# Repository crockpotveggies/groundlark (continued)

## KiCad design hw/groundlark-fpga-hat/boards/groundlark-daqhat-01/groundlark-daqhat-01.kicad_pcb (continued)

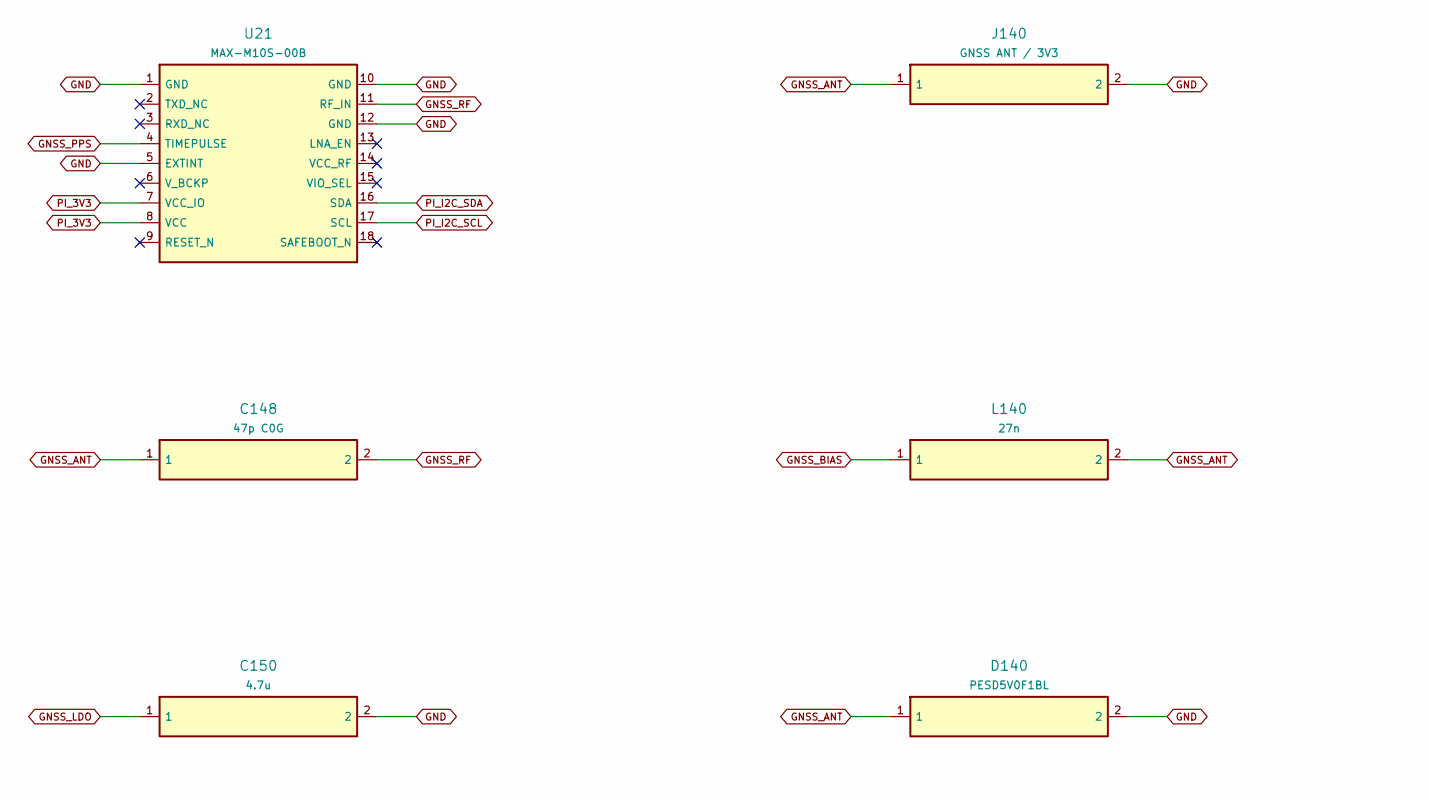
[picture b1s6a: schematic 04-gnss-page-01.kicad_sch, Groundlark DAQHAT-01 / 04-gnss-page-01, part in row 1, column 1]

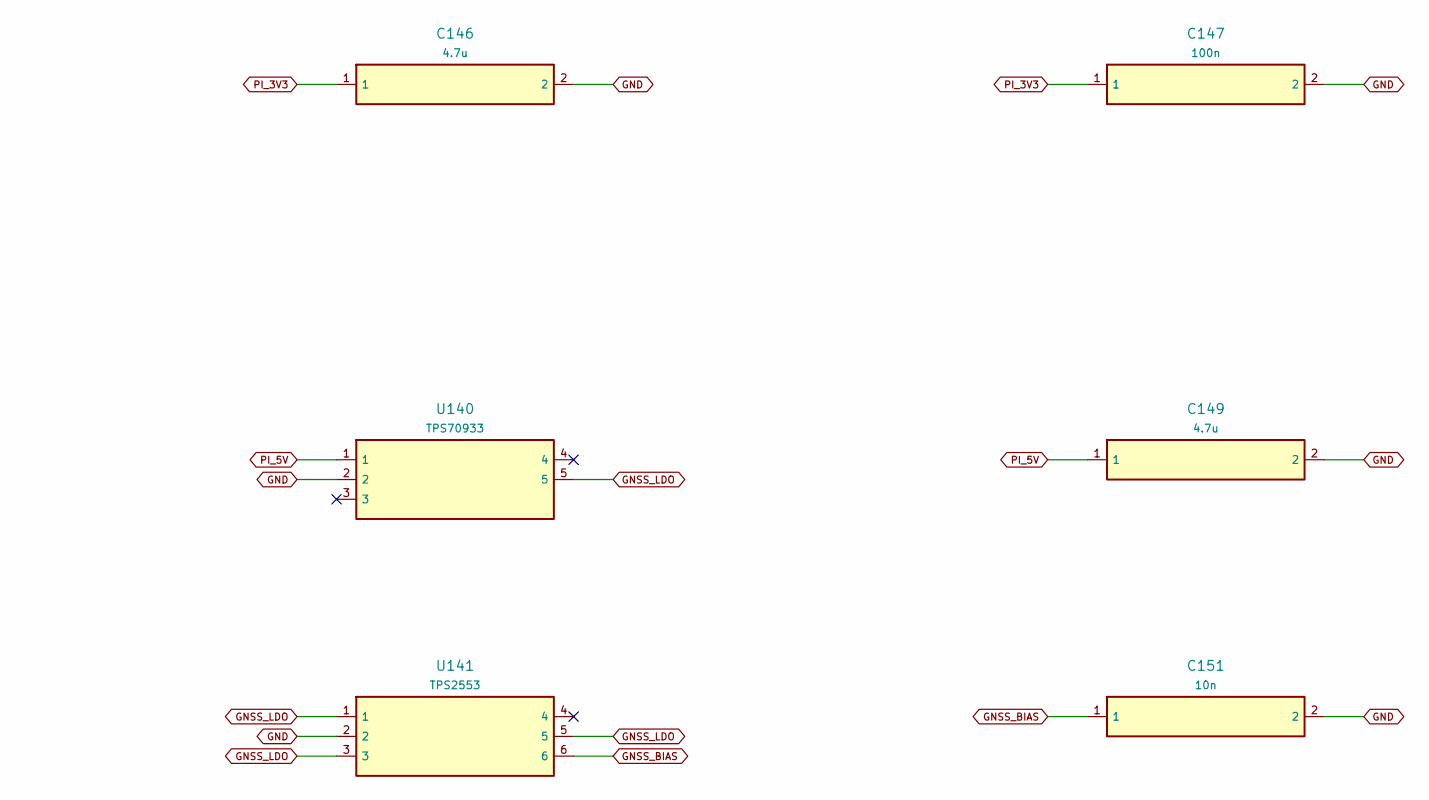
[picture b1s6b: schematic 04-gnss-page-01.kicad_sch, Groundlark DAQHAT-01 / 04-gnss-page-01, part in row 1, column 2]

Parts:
C146, C149, C150: 4.7u; Capacitor_SMD__C_0805_2012Metric; MPN GRM21BR71C475KA73L
C147: 100n; Capacitor_SMD__C_0603_1608Metric; MPN GRM188R71H104KA93D
C148: 47p C0G; GNSS_C0402; MPN GRM1555C1H470JA01D
C151: 10n; SUP_C_0603_1608Metric; MPN GRM188R71H103KA01D
D140: PESD5V0F1BL; GNSS_SOD882; MPN PESD5V0F1BL,315
J140: GNSS ANT / 3V3; GNSS_HL_SMA_KWE_02; MPN HL-SMA-KWE-02
L140: 27n; GNSS_L0402; MPN LQW15AN27NJ00D
U21: MAX-M10S-00B; RF_GPS__ublox_MAX; MPN MAX-M10S-00B
U140: TPS70933; SUP_SOT-23-5; MPN TPS70933DBVR
U141: TPS2553; GNSS_SOT23_6; MPN TPS2553DBVR

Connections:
GND: C146.2, C147.2, C149.2, C150.2, C151.2, D140.2, J140.2, U21.1 (GND), U21.5 (EXTINT), U21.10 (GND), U21.12 (GND), U140.2, U141.2; also elsewhere on the board
GNSS_ANT: C148.1, D140.1, J140.1, L140.2
GNSS_BIAS: C151.1, L140.1, U141.6
GNSS_FAULT_NC: U141.4
GNSS_LDO: C150.1, U140.5, U141.1, U141.3, U141.5; also elsewhere on the board
GNSS_PPS: U21.4 (TIMEPULSE); also elsewhere on the board
GNSS_RF: C148.2, U21.11 (RF_IN)
PI_3V3: C146.1, C147.1, U21.7 (VCC_IO), U21.8 (VCC); also elsewhere on the board
PI_5V: C149.1, U140.1; also elsewhere on the board
PI_I2C_SCL: U21.17 (SCL); also elsewhere on the board
PI_I2C_SDA: U21.16 (SDA); also elsewhere on the board
u21-2: U21.2 (TXD_NC)
u21-3: U21.3 (RXD_NC)
u21-6: U21.6 (V_BCKP)
u21-9: U21.9 (RESET_N)
u21-13: U21.13 (LNA_EN)
u21-14: U21.14 (VCC_RF)
u21-15: U21.15 (VIO_SEL)
u21-18: U21.18 (SAFEBOOT_N)
u140-3: U140.3
u140-4: U140.4

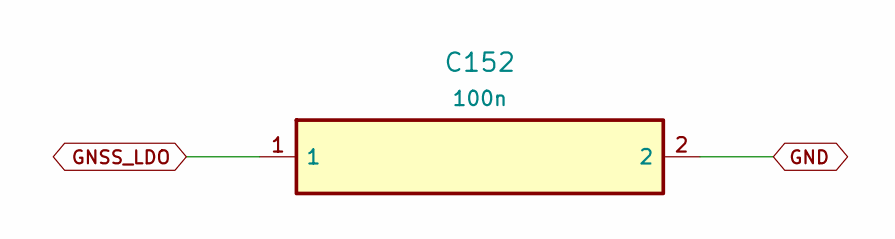
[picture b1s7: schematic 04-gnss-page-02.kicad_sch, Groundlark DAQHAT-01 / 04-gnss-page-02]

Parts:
C152: 100n; Capacitor_SMD__C_0603_1608Metric; MPN GRM188R71H104KA93D

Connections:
GND: C152.2; also elsewhere on the board
GNSS_LDO: C152.1; also elsewhere on the board

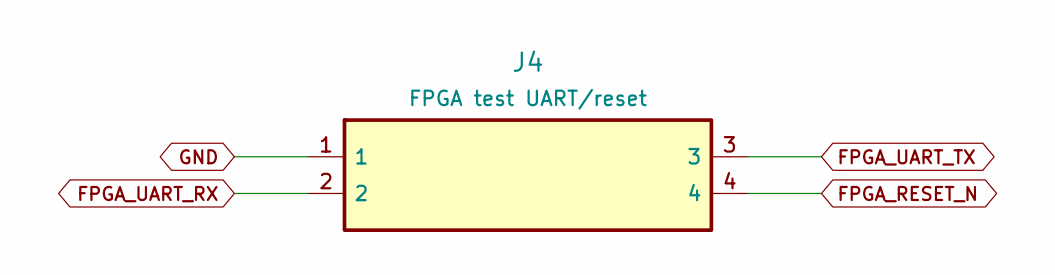
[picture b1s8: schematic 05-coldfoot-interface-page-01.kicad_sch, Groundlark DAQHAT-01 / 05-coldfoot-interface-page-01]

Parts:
J4: FPGA test UART/reset; Connector_PinHeader_2.54mm__PinHeader_1x04_P2.54mm_Vertical; MPN Coldfoot UART service ONLY

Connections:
FPGA_RESET_N: J4.4; also elsewhere on the board
FPGA_UART_RX: J4.2; also elsewhere on the board
FPGA_UART_TX: J4.3; also elsewhere on the board
GND: J4.1; also elsewhere on the board

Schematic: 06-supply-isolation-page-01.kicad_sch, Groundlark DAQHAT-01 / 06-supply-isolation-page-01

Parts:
C40: 10u; Capacitor_SMD__C_0805_2012Metric; MPN GRM21BR61A106KE19L
C41, C43, C44, C45, C46, C47: 100n; Capacitor_SMD__C_0603_1608Metric; MPN GRM188R71H104KA93D
C42: 22u; Capacitor_SMD__C_1206_3216Metric; MPN GRM31CR61A226KE19L
R50: 10k; Resistor_SMD__R_0603_1608Metric; MPN RC0603FR-0710KL
U40: TLV1117LV33DCYR; Package_TO_SOT_SMD__SOT-223-3_TabPin2; MPN TLV1117LV33DCYR
U41, U42: SN74LVC8T245PWR; Package_SO__TSSOP-24_4.4x7.8mm_P0.65mm; MPN SN74LVC8T245PWR

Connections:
GEO_DRDY_N: U42.16 (B6); also elsewhere on the board
GND: C40.2, C41.2, C42.2, C43.2, C44.2, C45.2, C46.2, C47.2, U40.1 (GND), U41.8 (A6), U41.9 (A7), U41.10 (A8), U41.11 (GND), U41.12 (GND), U41.13 (GND), U42.2 (DIR), U42.11 (GND), U42.12 (GND), U42.13 (GND), U42.14 (B8), U42.15 (B7), U42.17 (B5); also elsewhere on the board
IMU1_CS: U41.19 (B3); also elsewhere on the board
IMU1_INT: U42.20 (B2); also elsewhere on the board
IMU2_CS: U41.18 (B4); also elsewhere on the board
IMU2_INT: U42.19 (B3); also elsewhere on the board
IMU3_CS: U41.17 (B5); also elsewhere on the board
IMU3_INT: U42.18 (B4); also elsewhere on the board
PI_3V3: C44.1, C46.1, R50.2, U41.1 (VCCA), U41.2 (DIR), U42.1 (VCCA); also elsewhere on the board
PI_5V: C40.1, C41.1, U40.3 (IN); also elsewhere on the board
PI_GEO_DRDY_N: U42.8 (A6); also elsewhere on the board
PI_IMU1_CS: U41.5 (A3); also elsewhere on the board
PI_IMU1_INT: U42.4 (A2); also elsewhere on the board
PI_IMU2_CS: U41.6 (A4); also elsewhere on the board
PI_IMU2_INT: U42.5 (A3); also elsewhere on the board
PI_IMU3_CS: U41.7 (A5); also elsewhere on the board
PI_IMU3_INT: U42.6 (A4); also elsewhere on the board
PI_SPI_MISO: U42.3 (A1); also elsewhere on the board
PI_SPI_MOSI: U41.3 (A1); also elsewhere on the board
PI_SPI_SCLK: U41.4 (A2); also elsewhere on the board
SENSOR_OE_N: R50.1, U41.22 (OE_N), U42.22 (OE_N); also elsewhere on the board
SENS_3V3: C42.1, C43.1, C45.1, C47.1, U40.2 (OUT), U41.23 (VCCB), U41.24 (VCCB), U42.23 (VCCB), U42.24 (VCCB); also elsewhere on the board
SPI_MISO: U42.21 (B1); also elsewhere on the board
SPI_MOSI: U41.21 (B1); also elsewhere on the board
SPI_SCLK: U41.20 (B2); also elsewhere on the board
u41-14: U41.14 (B8)
u41-15: U41.15 (B7)
u41-16: U41.16 (B6)
u42-7: U42.7 (A5)
u42-9: U42.9 (A7)
u42-10: U42.10 (A8)

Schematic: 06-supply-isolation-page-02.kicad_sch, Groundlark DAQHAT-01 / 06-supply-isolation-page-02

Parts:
C48, C49: 100n; Capacitor_SMD__C_0603_1608Metric; MPN GRM188R71H104KA93D
R51: 100k; Resistor_SMD__R_0603_1608Metric; MPN RC0603FR-07100KL
R52, R53: 4.7k; Resistor_SMD__R_0603_1608Metric; MPN RC0603FR-074K7L
TP1: SENS_3V3; TestPoint__TestPoint_Pad_D1.5mm; MPN SENS_3V3
TP2: GND; TestPoint__TestPoint_Pad_D1.5mm; MPN GND
TP4: SENSOR_OE_N; TestPoint__TestPoint_Pad_D1.5mm; MPN SENSOR_OE_N
U43: ISO1640BDR; Package_SO__SOIC-8_3.9x4.9mm_P1.27mm; MPN ISO1640BDR

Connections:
GND: C48.2, C49.2, R51.2, TP2.1, U43.4 (GND1), U43.5 (GND2); also elsewhere on the board
I2C_SCL: R53.1, U43.3 (SCL1); also elsewhere on the board
I2C_SDA: R52.1, U43.2 (SDA1); also elsewhere on the board
PI_3V3: C49.1, U43.8 (VCC2); also elsewhere on the board
PI_I2C_SCL: U43.6 (SCL2); also elsewhere on the board
PI_I2C_SDA: U43.7 (SDA2); also elsewhere on the board
SENSOR_OE_N: TP4.1; also elsewhere on the board
SENS_3V3: C48.1, R52.2, R53.2, TP1.1, U43.1 (VCC1); also elsewhere on the board
SPI_MISO: R51.1; also elsewhere on the board

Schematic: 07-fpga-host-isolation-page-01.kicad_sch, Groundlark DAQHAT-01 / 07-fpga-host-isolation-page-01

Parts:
C75, C76, C77: 100n; Capacitor_SMD__C_0603_1608Metric; MPN GRM188R71H104KA93D
Q1: 2N7002; Package_TO_SOT_SMD__SOT-23; MPN 2N7002
R61: 47; Resistor_SMD__R_0603_1608Metric; MPN RC0603FR-0747RL
R62, R66: 100k; Resistor_SMD__R_0603_1608Metric; MPN RC0603FR-07100KL
R63, R64: 10k; Resistor_SMD__R_0603_1608Metric; MPN RC0603FR-0710KL
R65: 1k; Resistor_SMD__R_0603_1608Metric; MPN RC0603FR-071KL
U51: TXU0202DCUR; Package_SO__VSSOP-8_2.3x2mm_P0.5mm; MPN TXU0202DCUR
U52: TLV803EA30DBZR; Package_TO_SOT_SMD__SOT-23; MPN TLV803EA30DBZR

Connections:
FPGA_3V3: C76.1, C77.1, R63.2, R64.2, U51.7 (VCCB), U52.3 (VDD); also elsewhere on the board
FPGA_IO_ENABLE: R62.1, U51.6 (OE); also elsewhere on the board
FPGA_RESET_GATE: Q1.1 (G), R65.2, R66.1
FPGA_RESET_GPIO: R65.1; also elsewhere on the board
FPGA_RESET_N: Q1.3 (D), R64.1, U52.2 (RESET_N); also elsewhere on the board
FPGA_UART_DRIVE: R61.1, U51.8 (B1Y_OUT)
FPGA_UART_RX: R61.2, R63.1; also elsewhere on the board
FPGA_UART_TX: U51.1 (B2_IN); also elsewhere on the board
GND: C75.2, C76.2, C77.2, Q1.2 (S), R62.2, R66.2, U51.2 (GND), U52.1 (GND); also elsewhere on the board
PI_3V3: C75.1, U51.3 (VCCA); also elsewhere on the board
PI_UART_RX: U51.4 (A2Y_OUT); also elsewhere on the board
PI_UART_TX: U51.5 (A1_IN); also elsewhere on the board

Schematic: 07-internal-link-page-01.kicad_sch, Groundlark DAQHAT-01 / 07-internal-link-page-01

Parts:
C100, C101, C102, C103, C104, C105: 100n; Capacitor_SMD__C_0603_1608Metric; MPN GRM188R71H104KA93D
U100, U101: TMUX1574PWR; Package_SO__TSSOP-16_4.4x5mm_P0.65mm; MPN TMUX1574PWR
U102: TCA9534PWR; Package_SO__TSSOP-16_4.4x5mm_P0.65mm; MPN TCA9534PWR
U103: SN74LVC1G10DCKR; Package_TO_SOT_SMD__SOT-363_SC-70-6; MPN SN74LVC1G10DCKR
U104, U105: TLV809EA30DBZR; Package_TO_SOT_SMD__SOT-23; MPN TLV809EA30DBZR

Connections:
FPGA_3V3: C100.1, C101.1, C103.1, C105.1, U100.16 (VDD), U101.16 (VDD), U103.5 (VCC), U105.3 (VDD); also elsewhere on the board
FPGA_LINK_CS_N: U101.2 (S1A); also elsewhere on the board
FPGA_LINK_DQ0: U100.5 (S2A); also elsewhere on the board
FPGA_LINK_DQ1: U100.11 (S3A); also elsewhere on the board
FPGA_LINK_DQ2: U100.14 (S4A); also elsewhere on the board
FPGA_LINK_DQ3: U101.5 (S2A); also elsewhere on the board
FPGA_LINK_SCLK: U100.2 (S1A); also elsewhere on the board
GND: C100.2, C101.2, C102.2, C103.2, C104.2, C105.2, U100.8 (GND), U101.8 (GND), U101.9 (D3), U101.10 (S3B), U101.11 (S3A), U101.12 (D4), U101.13 (S4B), U101.14 (S4A), U102.1 (A0), U102.2 (A1), U102.3 (A2), U102.6 (P2), U102.7 (P3), U102.8 (GND), U102.9 (P4), U102.10 (P5), U102.11 (P6), U102.12 (P7), U103.2 (GND), U104.1 (GND), U105.1 (GND); also elsewhere on the board
JTAG_TCK: U100.3 (S1B); also elsewhere on the board
JTAG_TDI: U100.6 (S2B); also elsewhere on the board
JTAG_TDO: U100.10 (S3B); also elsewhere on the board
JTAG_TMS: U100.13 (S4B); also elsewhere on the board
LINK_ARMED_REQUEST: U103.1 (A); also elsewhere on the board
LINK_CS_N: U101.4 (D1); also elsewhere on the board
LINK_DQ0: U100.7 (D2); also elsewhere on the board
LINK_DQ1: U100.9 (D3); also elsewhere on the board
LINK_DQ2: U100.12 (D4); also elsewhere on the board
LINK_DQ3: U101.7 (D2); also elsewhere on the board
LINK_FPGA_GOOD: U103.6 (C), U105.2 (RESET_N); also elsewhere on the board
LINK_JTAG_SEL: U100.1 (SEL), U101.1 (SEL), U102.4 (P0_MODE); also elsewhere on the board
LINK_OE_N: U100.15 (EN_N), U101.15 (EN_N), U103.4 (Y); also elsewhere on the board
LINK_PI_GOOD: U103.3 (B), U104.2 (RESET_N); also elsewhere on the board
LINK_REQUEST: U102.5 (P1_ENABLE); also elsewhere on the board
LINK_SCLK: U100.4 (D1); also elsewhere on the board
PI_3V3: C102.1, C104.1, U102.16 (VCC), U104.3 (VDD); also elsewhere on the board
PI_I2C_SCL: U102.14 (SCL); also elsewhere on the board
PI_I2C_SDA: U102.15 (SDA); also elsewhere on the board
u101-3: U101.3 (S1B)
u101-6: U101.6 (S2B)
u102-13: U102.13 (INT_N)

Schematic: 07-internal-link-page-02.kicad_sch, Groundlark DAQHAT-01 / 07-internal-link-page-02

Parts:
R100, R101, R102, R103, R104, R105: 22; Resistor_SMD__R_0603_1608Metric; MPN RC0603FR-0722RL
R106, R107, R108, R109, R110, R111: 10k; Resistor_SMD__R_0603_1608Metric; MPN RC0603FR-0710KL

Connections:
FPGA_3V3: R108.2, R111.2; also elsewhere on the board
FPGA_LINK_CS_N: R111.1; also elsewhere on the board
GND: R106.2, R107.2, R109.2, R110.2; also elsewhere on the board
LINK_CS_N: R104.2; also elsewhere on the board
LINK_DQ0: R101.2; also elsewhere on the board
LINK_DQ1: R102.2; also elsewhere on the board
LINK_DQ2: R103.2; also elsewhere on the board
LINK_DQ3: R105.2; also elsewhere on the board
LINK_FPGA_GOOD: R110.1; also elsewhere on the board
LINK_JTAG_SEL: R106.1; also elsewhere on the board
LINK_OE_N: R108.1; also elsewhere on the board
LINK_PI_GOOD: R109.1; also elsewhere on the board
LINK_REQUEST: R107.1; also elsewhere on the board
LINK_SCLK: R100.2; also elsewhere on the board
PI_LINK_CS_N: R104.1; also elsewhere on the board
PI_LINK_DQ0: R101.1; also elsewhere on the board
PI_LINK_DQ1: R102.1; also elsewhere on the board
PI_LINK_DQ2: R103.1; also elsewhere on the board
PI_LINK_DQ3: R105.1; also elsewhere on the board
PI_LINK_SCLK: R100.1; also elsewhere on the board

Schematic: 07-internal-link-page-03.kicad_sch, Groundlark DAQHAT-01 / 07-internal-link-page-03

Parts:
C106: 100n; Capacitor_SMD__C_0603_1608Metric; MPN GRM188R71H104KA93D
R112, R114, R116, R117: 100k; Resistor_SMD__R_0603_1608Metric; MPN RC0603FR-07100KL
R113, R115: 10k; Resistor_SMD__R_0603_1608Metric; MPN RC0603FR-0710KL
U106: SN74LVC1G08DCKR; Package_TO_SOT_SMD__SOT-353_SC-70-5; MPN SN74LVC1G08DCKR

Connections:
FPGA_3V3: C106.1, R113.2, R115.2, U106.5 (VCC); also elsewhere on the board
FPGA_IO_ENABLE: U106.2 (B); also elsewhere on the board
FPGA_LINK_DQ2: R116.1; also elsewhere on the board
FPGA_LINK_DQ3: R117.1; also elsewhere on the board
FPGA_LINK_SCLK: R112.1; also elsewhere on the board
GND: C106.2, R112.2, R114.2, R116.2, R117.2, U106.3 (GND); also elsewhere on the board
JTAG_TCK: R114.1; also elsewhere on the board
JTAG_TDI: R115.1; also elsewhere on the board
JTAG_TMS: R113.1; also elsewhere on the board
LINK_ARMED_REQUEST: U106.4 (Y); also elsewhere on the board
LINK_REQUEST: U106.1 (A); also elsewhere on the board

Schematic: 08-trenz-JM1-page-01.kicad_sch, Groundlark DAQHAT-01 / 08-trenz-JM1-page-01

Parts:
J80: LSHM-150-04.0-L-DV-A-S-K-TR; TZ_TZ100; MPN LSHM-150-04.0-L-DV-A-S-K-TR

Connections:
3: J80.3
5: J80.5
9: J80.9
11: J80.11
15: J80.15
17: J80.17
18: J80.18
20: J80.20
21: J80.21
22: J80.22
23: J80.23
24: J80.24
26: J80.26
28: J80.28
32: J80.32
34: J80.34
35: J80.35
36: J80.36
37: J80.37
38: J80.38
39: J80.39
40: J80.40
41: J80.41
42: J80.42
44: J80.44
45: J80.45
46: J80.46
47: J80.47
48: J80.48
49: J80.49
50: J80.50
51: J80.51
52: J80.52
55: J80.55
56: J80.56
57: J80.57
58: J80.58
59: J80.59
60: J80.60
61: J80.61
62: J80.62
65: J80.65
66: J80.66
67: J80.67
68: J80.68
69: J80.69
70: J80.70
71: J80.71
72: J80.72
75: J80.75
76: J80.76
77: J80.77
78: J80.78
79: J80.79
80: J80.80
81: J80.81
82: J80.82
84: J80.84
85: J80.85
86: J80.86
87: J80.87
88: J80.88
91: J80.91
92: J80.92
93: J80.93
94: J80.94
95: J80.95
96: J80.96
97: J80.97
98: J80.98
99: J80.99
100: J80.100
FPGA_3V3: J80.10, J80.12, J80.13; also elsewhere on the board
FPGA_EN1: J80.27; also elsewhere on the board
FPGA_JTAGEN: J80.90; also elsewhere on the board
FPGA_MODE: J80.31
FPGA_NOSEQ: J80.8; also elsewhere on the board
FPGA_PGOOD: J80.29
FPGA_VIN: J80.2, J80.4, J80.6, J80.14, J80.16; also elsewhere on the board
GND: J80.1, J80.7, J80.19, J80.25, J80.30, J80.33, J80.43, J80.53, J80.54, J80.63, J80.64, J80.73, J80.74, J80.83, J80.89, J80.101; also elsewhere on the board

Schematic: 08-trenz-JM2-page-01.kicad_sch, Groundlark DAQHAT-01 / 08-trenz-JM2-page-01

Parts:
J81: LSHM-150-04.0-L-DV-A-S-K-TR; TZ_TZ100; MPN LSHM-150-04.0-L-DV-A-S-K-TR

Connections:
6: J81.6
16: J81.16
25: J81.25
27: J81.27
29: J81.29
30: J81.30
31: J81.31
33: J81.33
43: J81.43
53: J81.53
54: J81.54
63: J81.63
64: J81.64
73: J81.73
74: J81.74
83: J81.83
90: J81.90
FPGA_3V3: J81.2, J81.4, J81.8, J81.9, J81.10, J81.11, J81.92; also elsewhere on the board
FPGA_CONFIG_RESET_N: J81.17; also elsewhere on the board
FPGA_LINK_CS_N: J81.23; also elsewhere on the board
FPGA_LINK_DQ0: J81.22; also elsewhere on the board
FPGA_LINK_DQ1: J81.24; also elsewhere on the board
FPGA_LINK_DQ2: J81.26; also elsewhere on the board
FPGA_LINK_DQ3: J81.28; also elsewhere on the board
FPGA_LINK_SCLK: J81.21; also elsewhere on the board
FPGA_RESET_N: J81.13; also elsewhere on the board
FPGA_UART_RX: J81.12; also elsewhere on the board
FPGA_UART_TX: J81.14; also elsewhere on the board
FPGA_VIN: J81.1, J81.3, J81.5, J81.7; also elsewhere on the board
GND: J81.19, J81.39, J81.40, J81.49, J81.50, J81.59, J81.60, J81.69, J81.70, J81.79, J81.80, J81.89, J81.101; also elsewhere on the board
JTAG_TCK: J81.100; also elsewhere on the board
JTAG_TDI: J81.96; also elsewhere on the board
JTAG_TDO: J81.98; also elsewhere on the board
JTAG_TMS: J81.94; also elsewhere on the board
j81-15: J81.15
j81-18: J81.18
j81-20: J81.20
j81-32: J81.32
j81-34: J81.34
j81-35: J81.35
j81-36: J81.36
j81-37: J81.37
j81-38: J81.38
j81-41: J81.41
j81-42: J81.42
j81-44: J81.44
j81-45: J81.45
j81-46: J81.46
j81-47: J81.47
j81-48: J81.48
j81-51: J81.51
j81-52: J81.52
j81-55: J81.55
j81-56: J81.56
j81-57: J81.57
j81-58: J81.58
j81-61: J81.61
j81-62: J81.62
j81-65: J81.65
j81-66: J81.66
j81-67: J81.67
j81-68: J81.68
j81-71: J81.71
j81-72: J81.72
j81-75: J81.75
j81-76: J81.76
j81-77: J81.77
j81-78: J81.78
j81-81: J81.81
j81-82: J81.82
j81-84: J81.84
j81-85: J81.85
j81-86: J81.86
j81-87: J81.87
j81-88: J81.88
j81-91: J81.91
j81-93: J81.93
j81-95: J81.95
j81-97: J81.97
j81-99: J81.99

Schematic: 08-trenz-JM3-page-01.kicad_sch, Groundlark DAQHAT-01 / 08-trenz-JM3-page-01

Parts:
J82: LSHM-130-04.0-L-DV-A-S-K-TR; TZ_TZ60; MPN LSHM-130-04.0-L-DV-A-S-K-TR

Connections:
1: J82.1
2: J82.2
4: J82.4
7: J82.7
8: J82.8
10: J82.10
13: J82.13
14: J82.14
19: J82.19
GND: J82.5, J82.6, J82.11, J82.12, J82.17, J82.18, J82.23, J82.24, J82.29, J82.30, J82.35, J82.36, J82.45, J82.46, J82.61; also elsewhere on the board
j82-3: J82.3
j82-9: J82.9
j82-15: J82.15
j82-16: J82.16
j82-20: J82.20
j82-21: J82.21
j82-22: J82.22
j82-25: J82.25
j82-26: J82.26
j82-27: J82.27
j82-28: J82.28
j82-31: J82.31
j82-32: J82.32
j82-33: J82.33
j82-34: J82.34
j82-37: J82.37
j82-38: J82.38
j82-39: J82.39
j82-40: J82.40
j82-41: J82.41
j82-42: J82.42
j82-43: J82.43
j82-44: J82.44
j82-47: J82.47
j82-48: J82.48
j82-49: J82.49
j82-50: J82.50
j82-51: J82.51
j82-52: J82.52
j82-53: J82.53
j82-54: J82.54
j82-55: J82.55
j82-56: J82.56
j82-57: J82.57
j82-58: J82.58
j82-59: J82.59
j82-60: J82.60

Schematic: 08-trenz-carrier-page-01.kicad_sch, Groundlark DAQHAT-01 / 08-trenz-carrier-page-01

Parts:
JP80, JP81: TSW-102-07-G-S; TZ_TZ_JP; MPN TSW-102-07-G-S
R80, R81: 10k; Resistor_SMD__R_0603_1608Metric; MPN RC0603FR-0710KL

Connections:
FPGA_CONFIG_RESET_N: JP81.1; also elsewhere on the board
FPGA_EN1: JP80.1; also elsewhere on the board
FPGA_JTAGEN: R80.1; also elsewhere on the board
FPGA_NOSEQ: R81.1; also elsewhere on the board
GND: JP80.2, JP81.2, R80.2, R81.2; also elsewhere on the board

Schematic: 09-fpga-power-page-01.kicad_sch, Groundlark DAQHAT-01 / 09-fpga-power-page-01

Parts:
C80, C81, C82: 22u; Capacitor_SMD__C_1206_3216Metric; MPN GRM31CR61A226KE19L
C83: 100n; Capacitor_SMD__C_0603_1608Metric; MPN GRM188R71H104KA93D
C84, C85: 4.7u; Capacitor_SMD__C_0805_2012Metric; MPN GRM21BR71A475KA73L
D80: B340A; PWR_D_SMA; MPN B340A-13-F
D81: SMAJ15A; PWR_D_SMA; MPN SMAJ15A-13-F
F80: 0466002.NRHF; PWR_Fuse_1206_3216Metric; MPN 0466002.NRHF
J83: 12V DC / CENTER +; PWR_BarrelJack_CUI_PJ-102AH_Horizontal; MPN PJ-102AH
R120: 10k; PWR_R_0603_1608Metric; MPN RT0603BRD0710KL
U80: TPSM53603; PWR_Texas_B3QFN-14-1EP_5x5.5mm_P0.65mm; MPN TPSM53603RDAR

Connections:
BUCK_EN: U80.2 (EN); also elsewhere on the board
BUCK_FB: R120.2, U80.9 (FB); also elsewhere on the board
EXT_12V: F80.1, J83.1 (CENTER)
FPGA_3V3: C84.1, C85.1; also elsewhere on the board
FPGA_EN1: U80.6 (PGOOD); also elsewhere on the board
FPGA_VIN: C80.1, C81.1, C82.1, C83.1, R120.1, U80.7 (VOUT), U80.8 (VOUT); also elsewhere on the board
FUSED_12V: D80.2 (A), F80.2
GND: C80.2, C81.2, C82.2, C83.2, C84.2, C85.2, D81.2 (A), J83.2 (SLEEVE), U80.3 (NC_GND), U80.10 (NC_GND), U80.11 (NC_GND), U80.12 (AGND), U80.15 (PGND); also elsewhere on the board
PROTECTED_12V: D80.1 (K), D81.1 (K), U80.1 (VIN), U80.14 (VIN); also elsewhere on the board
j83-3: J83.3 (SWITCH_NC)
u80-4: U80.4 (DNC)
u80-5: U80.5 (DNC)
u80-13: U80.13 (V5V)

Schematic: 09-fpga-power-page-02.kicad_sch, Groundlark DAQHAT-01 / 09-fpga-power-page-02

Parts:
C86, C87: 10u; PWR_C_1206_3216Metric; MPN CGA5L1X7R1H106K160AC
C88: 100n; PWR_C_0603_1608Metric; MPN GRM188R71H104KA93D
C89: 47u; PWR_CP_Elec_6.3x7.7; MPN EEE-FK1V470P
C110, C111, C112: 22u; PWR_C_1210_3225Metric; MPN GRM32ER71E226KE15L
R121: 4.30k; PWR_R_0603_1608Metric; MPN RT0603BRD074K3L
R122: 100k; PWR_R_0603_1608Metric; MPN RC0603FR-07100KL
R123: 15k; PWR_R_0603_1608Metric; MPN RC0603FR-0715KL
R124: 10k; PWR_R_0603_1608Metric; MPN RT0603BRD0710KL
SW80: FPGA OFF / ON; PWR_SW_SPDT_PCM12; MPN PCM12SMTR

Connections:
BUCK_EN: R122.2, R123.1, SW80.2; also elsewhere on the board
BUCK_FB: R121.1; also elsewhere on the board
FPGA_EN1: R124.2; also elsewhere on the board
FPGA_VIN: C110.1, C111.1, C112.1, R124.1; also elsewhere on the board
GND: C86.2, C87.2, C88.2, C89.2, C110.2, C111.2, C112.2, R121.2, R123.2, SW80.1; also elsewhere on the board
PROTECTED_12V: C86.1, C87.1, C88.1, C89.1, R122.1; also elsewhere on the board
sw80-3: SW80.3

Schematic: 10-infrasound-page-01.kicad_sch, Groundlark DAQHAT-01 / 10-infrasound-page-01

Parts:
C24: 100n; Capacitor_SMD__C_0603_1608Metric; MPN GRM188R71H104KA93D
U23: DLVR-F50D; Groundlark__DLVR_E1BS; MPN DLVR-F50D-E1BS-I-NI3F

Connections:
GND: C24.2, U23.1 (GND); also elsewhere on the board
I2C_SCL: U23.4 (SCL); also elsewhere on the board
I2C_SDA: U23.3 (SDA); also elsewhere on the board
SENS_3V3: C24.1, U23.2 (VS_3V3); also elsewhere on the board

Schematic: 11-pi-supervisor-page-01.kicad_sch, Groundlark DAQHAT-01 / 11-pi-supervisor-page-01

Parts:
C130: 4.7u; SUP_C_0805_2012Metric; MPN GRM21BR71C475KA73L
C131, C132, C133: 10u; PWR_C_1206_3216Metric; MPN CGA5L1X7R1H106K160AC
C134: 100n; PWR_C_0603_1608Metric; MPN GRM188R71H104KA93D
C135: 47u; PWR_CP_Elec_6.3x7.7; MPN EEE-FK1V470P
D130: B340A; PWR_D_SMA; MPN B340A-13-F
D131: SMAJ18A; SUP_D_SMA; MPN SMAJ18A-13-F
F130: 4A fuse; SUP_Fuse_1206_3216Metric; MPN 0466004.NRHF
J130: PI BATTERY 8-18V; SUP_PhoenixContact_MC_1,5_2-G-3.81_1x02_P3.81mm_Horizontal; MPN 1803277
U131: TPS70933; SUP_SOT-23-5; MPN TPS70933DBVR
U132: TPSM53603; PWR_Texas_B3QFN-14-1EP_5x5.5mm_P0.65mm; MPN TPSM53603RDAR

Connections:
BAT_FUSED: D130.2, F130.2; also elsewhere on the board
BAT_INPUT: F130.1, J130.1 (+)
BAT_PROTECTED: C131.1, C132.1, C133.1, C134.1, C135.1, D130.1, D131.1, U131.1 (IN), U132.1 (VIN), U132.14 (VIN)
GND: C130.2, C131.2, C132.2, C133.2, C134.2, C135.2, D131.2, J130.2 (GND), U131.2 (GND), U132.3 (NC_GND), U132.10 (NC_GND), U132.11 (NC_GND), U132.12 (AGND), U132.15 (PGND); also elsewhere on the board
PI_BUCK_FB: U132.9 (FB); also elsewhere on the board
PI_RAW_5V: U132.7 (VOUT), U132.8 (VOUT); also elsewhere on the board
SUP_3V3: C130.1, U131.5 (OUT); also elsewhere on the board
SUP_RUN: U132.2 (EN); also elsewhere on the board
u131-3: U131.3 (EN_FLOAT)
u131-4: U131.4 (NC)
u132-4: U132.4 (DNC)
u132-5: U132.5 (DNC)
u132-6: U132.6 (PGOOD_NC)
u132-13: U132.13 (V5V_NC)

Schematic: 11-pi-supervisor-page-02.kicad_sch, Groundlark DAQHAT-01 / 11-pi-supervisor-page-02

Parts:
C136, C137, C138: 22u; PWR_C_1210_3225Metric; MPN GRM32ER71E226KE15L
C139: 10n; SUP_C_0603_1608Metric; MPN GRM188R71H103KA01D
C140: 10u; SUP_C_0805_2012Metric; MPN GRM21BR61C106KE15L
C141: 100n; PWR_C_0603_1608Metric; MPN GRM188R71H104KA93D
R130: 10k; PWR_R_0603_1608Metric; MPN RT0603BRD0710KL
R131: 2.43k; SUP_R_0603_1608Metric; MPN RT0603BRD072K43L
R132: 100k; PWR_R_0603_1608Metric; MPN RC0603FR-07100KL
R133: 2k; SUP_R_0603_1608Metric; MPN RC0603FR-072KL
U130: MSPM0L1106; SUP_QFN-32-1EP_5x5mm_P0.5mm_EP3.45x3.45mm; MPN MSPM0L1106TRHBR
U133: TPS22953; SUP_Texas_WSON10_DQC0010A; MPN TPS22953DQCR

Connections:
12: U130.12
GND: C136.2, C137.2, C138.2, C139.2, C140.2, C141.2, R131.2, R132.2, R133.2, U130.5 (VSS), U130.33 (GND), U133.5 (GND), U133.7 (PG_NC), U133.11 (GND); also elsewhere on the board
PI_5V: C140.1, R133.1, U133.9 (OUT), U133.10 (OUT); also elsewhere on the board
PI_BUCK_FB: R130.2, R131.1; also elsewhere on the board
PI_RAW_5V: C136.1, C137.1, C138.1, R130.1, U133.1 (IN), U133.2 (IN), U133.3 (BIAS), U133.8 (SNS); also elsewhere on the board
PI_SWITCH_CT: C139.1, U133.6 (CT)
SUP_3V3: C141.1, U130.4 (VDD); also elsewhere on the board
SUP_ACK_N: U130.9 (PA5_ACK_N); also elsewhere on the board
SUP_BAT_ADC: U130.31 (PA27_A0); also elsewhere on the board
SUP_CORE: U130.32 (VCORE); also elsewhere on the board
SUP_NRST: U130.3 (NRST); also elsewhere on the board
SUP_REQUEST: U130.8 (PA4_SHUTDOWN); also elsewhere on the board
SUP_RUN: R132.1, U133.4 (EN); also elsewhere on the board
SUP_RUN_DRIVE: U130.7 (PA3_RUN); also elsewhere on the board
SUP_SWCLK: U130.24 (PA20_SWCLK); also elsewhere on the board
SUP_SWDIO: U130.23 (PA19_SWDIO); also elsewhere on the board
u130-1: U130.1
u130-2: U130.2
u130-6: U130.6
u130-10: U130.10
u130-11: U130.11
u130-13: U130.13
u130-14: U130.14
u130-15: U130.15
u130-16: U130.16
u130-17: U130.17
u130-18: U130.18
u130-19: U130.19
u130-20: U130.20
u130-21: U130.21
u130-22: U130.22
u130-25: U130.25
u130-26: U130.26
u130-27: U130.27
u130-28: U130.28
u130-29: U130.29
u130-30: U130.30

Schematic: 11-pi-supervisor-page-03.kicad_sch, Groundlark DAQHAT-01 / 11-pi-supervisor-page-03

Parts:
C142: 10u; SUP_C_0805_2012Metric; MPN GRM21BR61C106KE15L
C143: 470n; SUP_C_0603_1608Metric; MPN GRM188R71C474KA88D
C144, C145: 10n; SUP_C_0603_1608Metric; MPN GRM188R71H103KA01D
Q130, Q131: 2N7002; SUP_SOT-23; MPN 2N7002,215
R134: 47k; SUP_R_0603_1608Metric; MPN RC0603FR-0747KL
R135: 1M; SUP_R_0603_1608Metric; MPN RT0603BRD071ML
R136: 150k; SUP_R_0603_1608Metric; MPN RT0603BRD07150KL
R137, R139: 100k; PWR_R_0603_1608Metric; MPN RC0603FR-07100KL
R138: 10k; PWR_R_0603_1608Metric; MPN RT0603BRD0710KL

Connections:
BAT_FUSED: R135.1; also elsewhere on the board
GND: C142.2, C143.2, C144.2, C145.2, Q130.2 (S), Q131.2 (S), R136.2, R137.2, R139.2; also elsewhere on the board
PI_3V3: R138.1; also elsewhere on the board
PI_HALTED: Q131.1 (G), R139.1; also elsewhere on the board
PI_SHUTDOWN_N: Q130.3 (D), R138.2; also elsewhere on the board
SUP_3V3: C142.1, R134.2; also elsewhere on the board
SUP_ACK_N: Q131.3 (D); also elsewhere on the board
SUP_BAT_ADC: C145.1, R135.2, R136.1; also elsewhere on the board
SUP_CORE: C143.1; also elsewhere on the board
SUP_NRST: C144.1, R134.1; also elsewhere on the board
SUP_REQUEST: Q130.1 (G), R137.1; also elsewhere on the board

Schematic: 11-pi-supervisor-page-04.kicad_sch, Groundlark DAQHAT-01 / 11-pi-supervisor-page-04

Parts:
J131: SWD / 3V3 REF; SUP_PinHeader_1x05_P1.27mm_Vertical; MPN FTS-105-01-L-S
JP130: BENCH RUN; SUP_PinHeader_1x02_P2.54mm_Vertical; MPN TSW-102-07-G-S
R140: 100k; PWR_R_0603_1608Metric; MPN RC0603FR-07100KL
R141: 10k; PWR_R_0603_1608Metric; MPN RT0603BRD0710KL

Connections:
GND: J131.2 (GND); also elsewhere on the board
SUP_3V3: J131.1 (VTREF), JP130.1, R140.1; also elsewhere on the board
SUP_ACK_N: R140.2; also elsewhere on the board
SUP_NRST: J131.5 (NRST); also elsewhere on the board
SUP_RUN: JP130.2, R141.2; also elsewhere on the board
SUP_RUN_DRIVE: R141.1; also elsewhere on the board
SUP_SWCLK: J131.3 (SWCLK); also elsewhere on the board
SUP_SWDIO: J131.4 (SWDIO); also elsewhere on the board
